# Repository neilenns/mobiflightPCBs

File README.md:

# mobiflightPCBs
Assorted PCBs for Mobiflight

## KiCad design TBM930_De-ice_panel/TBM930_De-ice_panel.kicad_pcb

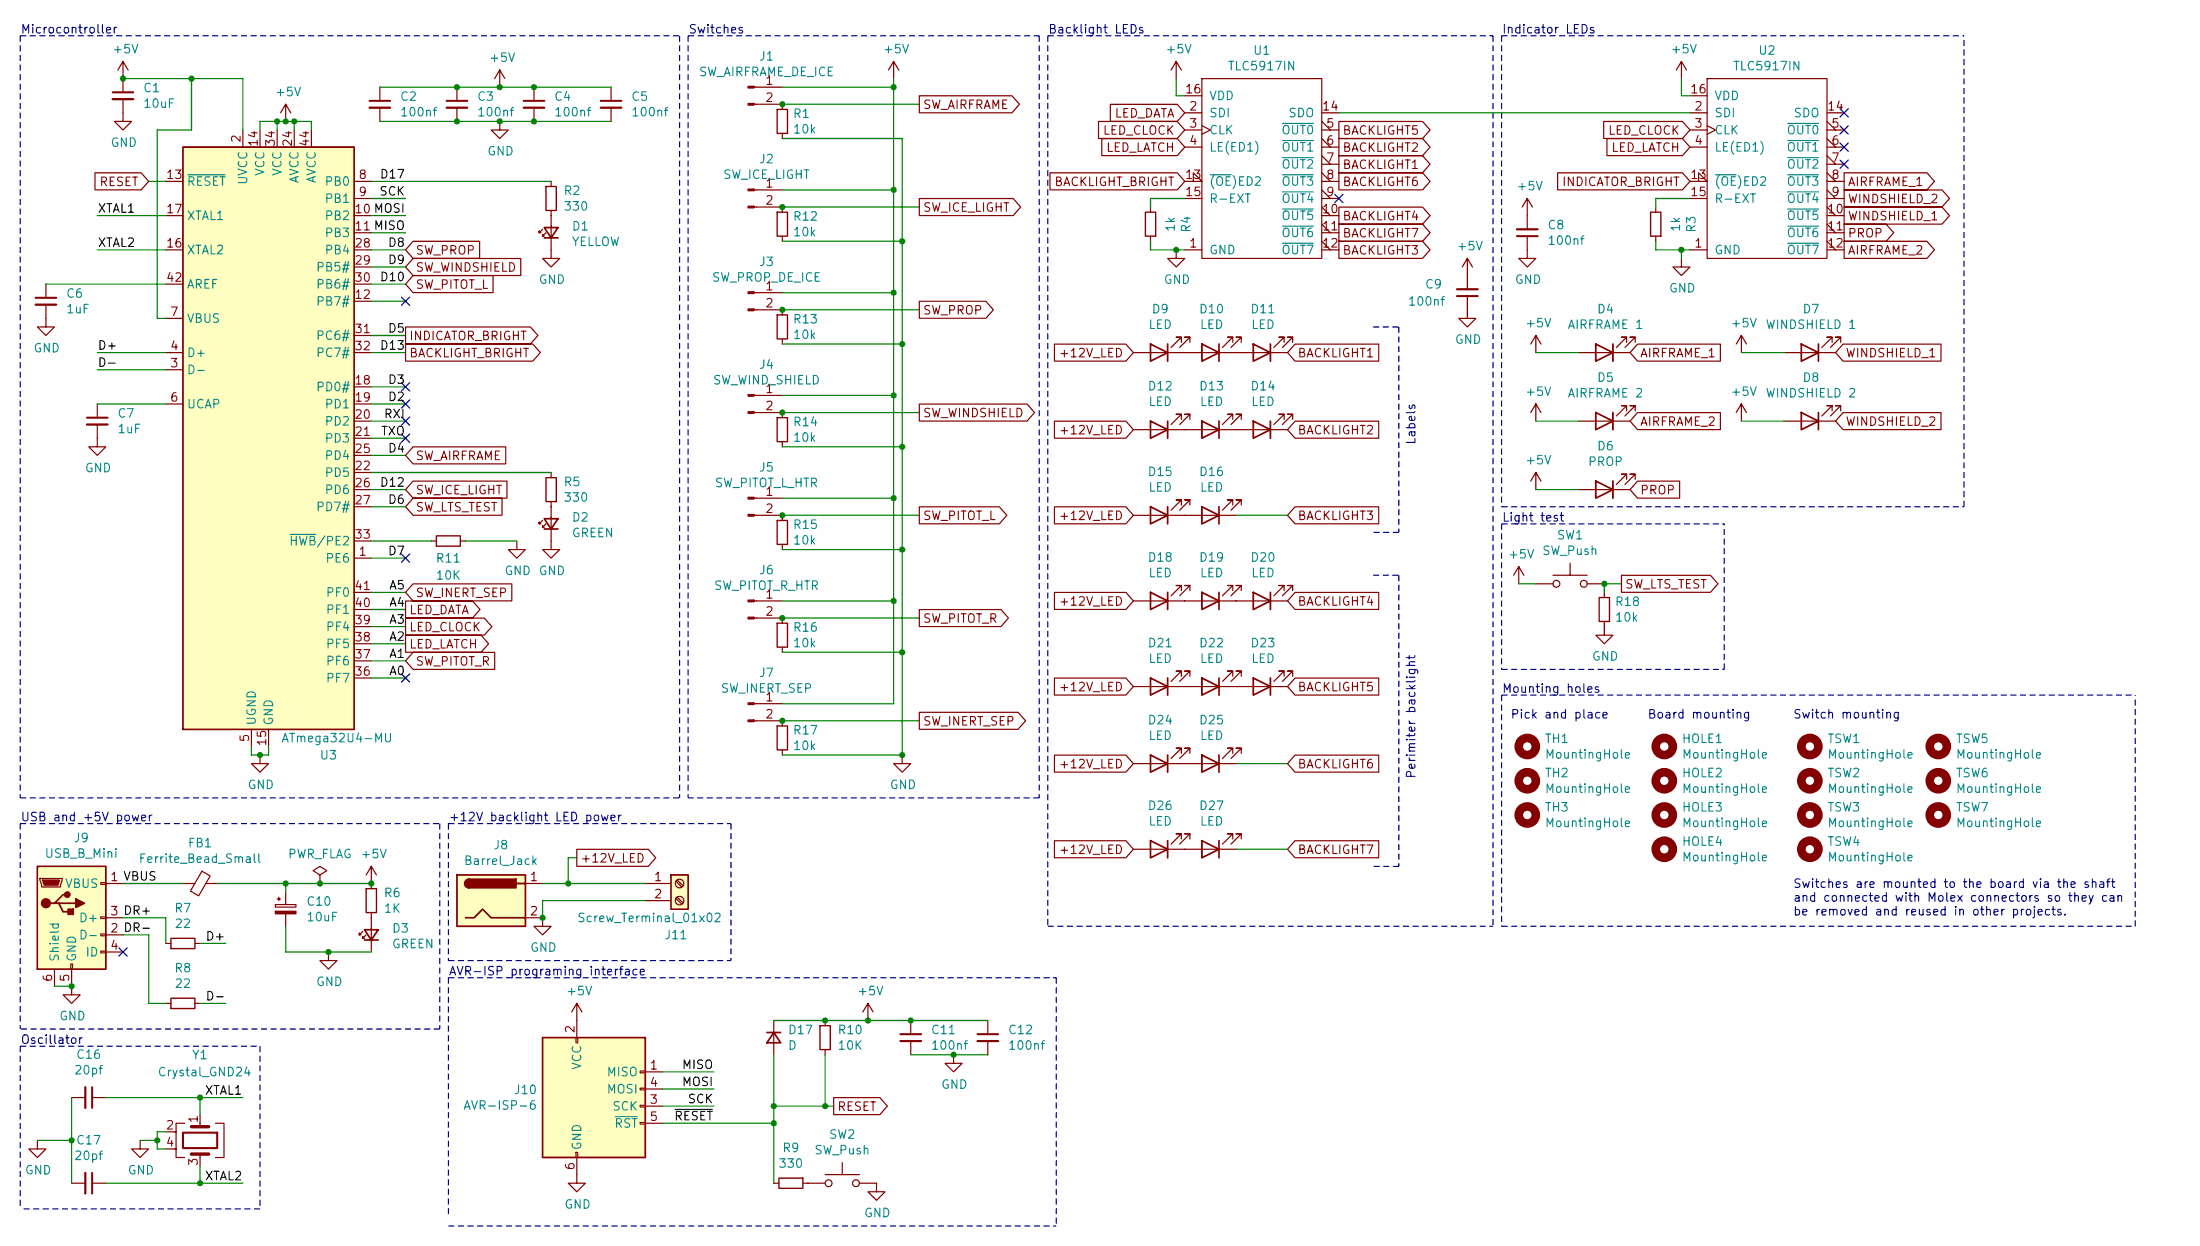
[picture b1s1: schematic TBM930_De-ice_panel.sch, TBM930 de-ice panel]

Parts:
C1, C10: 10uF; C_0603_1608Metric; JLC 0603
C2, C3, C4, C5, C8, C9, C11, C12: 100nf; C_0402_1005Metric; JLC 0402
C6, C7: 1uF; C_0402_1005Metric; JLC 0402
C16, C17: 20pf; C_0402_1005Metric; JLC 0402
D1: YELLOW; LED_0603_1608Metric; JLC LED_0603
D2, D3: GREEN; LED_0603_1608Metric; JLC LED_0603
D4: AIRFRAME 1; LED_D5.0mm
D5: AIRFRAME 2; LED_D5.0mm
D6: PROP; LED_D5.0mm
D7: WINDSHIELD 1; LED_D5.0mm
D8: WINDSHIELD 2; LED_D5.0mm
D9, D10, D11, D12, D13, D14, D15, D16, D18, D19, D20, D21, D22, D23, D24, D25, D26, D27: LED; LED_1206_3216Metric_Pad1.42x1.75mm_HandSolder
D17: D; D_SOD-323F; JLC SOD-323F
FB1: Ferrite_Bead_Small; C_0805_2012Metric; JLC 0805
HOLE1, HOLE2, HOLE3, HOLE4: MountingHole; MountingHole_3.2mm_M3
J1: SW_AIRFRAME_DE_ICE; Molex_KK-254_AE-6410-02A_1x02_P2.54mm_Vertical
J2: SW_ICE_LIGHT; Molex_KK-254_AE-6410-02A_1x02_P2.54mm_Vertical
J3: SW_PROP_DE_ICE; Molex_KK-254_AE-6410-02A_1x02_P2.54mm_Vertical
J4: SW_WIND_SHIELD; Molex_KK-254_AE-6410-02A_1x02_P2.54mm_Vertical
J5: SW_PITOT_L_HTR; Molex_KK-254_AE-6410-02A_1x02_P2.54mm_Vertical
J6: SW_PITOT_R_HTR; Molex_KK-254_AE-6410-02A_1x02_P2.54mm_Vertical
J7: SW_INERT_SEP; Molex_KK-254_AE-6410-02A_1x02_P2.54mm_Vertical
J8: Barrel_Jack; BarrelJack_Horizontal
J9: USB_B_Mini; USB_B_Mini_Amphenol_UE25BE5510H
J10: AVR-ISP-6; PinHeader_2x03_P2.54mm_Vertical
J11: Screw_Terminal_01x02; TerminalBlock_Phoenix_PT-1,5-2-5.0-H_1x02_P5.00mm_Horizontal
R1, R12, R13, R14, R15, R16, R17, R18: 10k; R_0402_1005Metric; JLC 0402
R2, R5, R9: 330; R_0402_1005Metric; JLC 0402
R3, R4: 1k; R_Axial_DIN0207_L6.3mm_D2.5mm_P7.62mm_Horizontal
R6: 1K; R_0402_1005Metric; JLC 0402
R7, R8: 22; R_0402_1005Metric; JLC 0402
R10, R11: 10K; R_0402_1005Metric; JLC 0402
SW1: SW_Push; SW_PUSH_6mm_H9.5mm
SW2: SW_Push; SW_PUSH_6mm_H4.3mm
TH1, TH2, TH3: MountingHole; JLCPCB_Tooling_Hole
TSW1, TSW2, TSW3, TSW4, TSW5, TSW6, TSW7: MountingHole; MiniToggleSPDT_screw_mount
U1, U2: TLC5917IN; DIP-16_W7.62mm
U3: ATmega32U4-MU; TQFP-44-1EP_10x10mm_P0.8mm_EP4.5x4.5mm
Y1: Crystal_GND24; Crystal_SMD_3225-4Pin_3.2x2.5mm; JLC SMD-CRY-3225_4P

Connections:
+5V: C1.1, C2.1, C3.1, C4.1, C5.1, C8.2, C9.2, C10.1, C11.1, C12.1, D4.2 (A), D5.2 (A), D6.2 (A), D7.2 (A), D8.2 (A), D17.1 (K), FB1.1, J1.1, J2.1, J3.1, J4.1, J5.1, J6.1, J7.1, J10.2 (VCC), R6.1, R10.1, SW1.1, U1.16 (VDD), U2.16 (VDD), U3.2 (UVCC), U3.7 (VBUS), U3.14 (VCC), U3.24 (AVCC), U3.34 (VCC), U3.44 (AVCC)
+12V_LED: D9.2 (A), D12.2 (A), D15.2 (A), D18.2 (A), D21.2 (A), D24.2 (A), D26.2 (A), J8.1, J11.1
/A0: U3.36 (PF7)
/D2: U3.19 (PD1)
/D3: U3.18 (PD0#)
/D7: U3.1 (PE6)
/D17: R2.1, U3.8 (PB0)
/D+: R7.2, U3.4 (D+)
/D-: R8.2, U3.3 (D-)
/DR+: J9.3 (D+), R7.1
/DR-: J9.2 (D-), R8.1
/MISO: J10.1 (MISO), U3.11 (PB3)
/MOSI: J10.4 (MOSI), U3.10 (PB2)
/RXI: U3.20 (PD2)
/SCK: J10.3 (SCK), U3.9 (PB1)
/TXO: U3.21 (PD3)
/VBUS: FB1.2, J9.1 (VBUS)
/XTAL1: C16.1, U3.17 (XTAL1), Y1.1
/XTAL2: C17.1, U3.16 (XTAL2), Y1.3
AIRFRAME_1: D4.1 (K), U2.8 (~OUT3)
AIRFRAME_2: D5.1 (K), U2.12 (~OUT7)
BACKLIGHT1: D11.1 (K), U1.7 (~OUT2)
BACKLIGHT2: D14.1 (K), U1.6 (~OUT1)
BACKLIGHT3: D16.1 (K), U1.12 (~OUT7)
BACKLIGHT4: D20.1 (K), U1.10 (~OUT5)
BACKLIGHT5: D23.1 (K), U1.5 (~OUT0)
BACKLIGHT6: D25.1 (K), U1.8 (~OUT3)
BACKLIGHT7: D27.1 (K), U1.11 (~OUT6)
BACKLIGHT_BRIGHT: U1.13 (~(OE)ED2), U3.32 (PC7#)
GND: C1.2, C2.2, C3.2, C4.2, C5.2, C6.2, C7.2, C8.1, C9.1, C10.2, C11.2, C12.2, C16.2, C17.2, D1.1 (K), D2.1 (K), D3.1 (K), J8.2, J9.5 (GND), J9.6 (Shield), J10.6 (GND), J11.2, R1.2, R3.1, R4.1, R11.2, R12.2, R13.2, R14.2, R15.2, R16.2, R17.2, R18.1, SW2.2, U1.1 (GND), U2.1 (GND), U3.5 (UGND), U3.15 (GND), U3.23 (GND), U3.35 (GND), U3.43 (GND), U3.45 (GND), Y1.2, Y1.4
INDICATOR_BRIGHT: U2.13 (~(OE)ED2), U3.31 (PC6#)
LED_CLOCK: U1.3 (CLK), U2.3 (CLK), U3.39 (PF4)
LED_DATA: U1.2 (SDI), U3.40 (PF1)
LED_LATCH: U1.4 (LE(ED1)), U2.4 (LE(ED1)), U3.38 (PF5)
unnamed: C6.1, U3.42 (AREF)
unnamed: C7.1, U3.6 (UCAP)
unnamed: D1.2 (A), R2.2
unnamed: D2.2 (A), R5.1
unnamed: D3.2 (A), R6.2
unnamed: D10.1 (K), D11.2 (A)
unnamed: D9.1 (K), D10.2 (A)
unnamed: D12.1 (K), D13.2 (A)
unnamed: D13.1 (K), D14.2 (A)
unnamed: D15.1 (K), D16.2 (A)
unnamed: D18.1 (K), D19.2 (A)
unnamed: D19.1 (K), D20.2 (A)
unnamed: D21.1 (K), D22.2 (A)
unnamed: D22.1 (K), D23.2 (A)
unnamed: D24.1 (K), D25.2 (A)
unnamed: D26.1 (K), D27.2 (A)
unnamed: R3.2, U2.15 (R-EXT)
unnamed: R4.2, U1.15 (R-EXT)
unnamed: R5.2, U3.22 (PD5)
unnamed: R9.1, SW2.1
unnamed: R11.1, U3.33 (~HWB~/PE2)
unnamed: U1.14 (SDO), U2.2 (SDI)
PROP: D6.1 (K), U2.11 (~OUT6)
RESET: D17.2 (A), J10.5 (~RST), R9.2, R10.2, U3.13 (~RESET)
SW_AIRFRAME: J1.2, R1.1, U3.25 (PD4)
SW_ICE_LIGHT: J2.2, R12.1, U3.26 (PD6)
SW_INERT_SEP: J7.2, R17.1, U3.41 (PF0)
SW_LTS_TEST: R18.2, SW1.2, U3.27 (PD7#)
SW_PITOT_L: J5.2, R15.1, U3.30 (PB6#)
SW_PITOT_R: J6.2, R16.1, U3.37 (PF6)
SW_PROP: J3.2, R13.1, U3.28 (PB4)
SW_WINDSHIELD: J4.2, R14.1, U3.29 (PB5#)
WINDSHIELD_1: D7.1 (K), U2.10 (~OUT5)
WINDSHIELD_2: D8.1 (K), U2.9 (~OUT4)

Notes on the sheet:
Switches
Switches are mounted to the board via the shaft and connected with Molex connectors so they can be removed and reused in other projects.
+12V backlight LED power
Backlight LEDs
USB and +5V power
Oscillator
Microcontroller
AVR-ISP programing interface
Labels
Perimiter backlight
Light test
Indicator LEDs
Pick and place
Board mounting
Switch mounting
Mounting holes

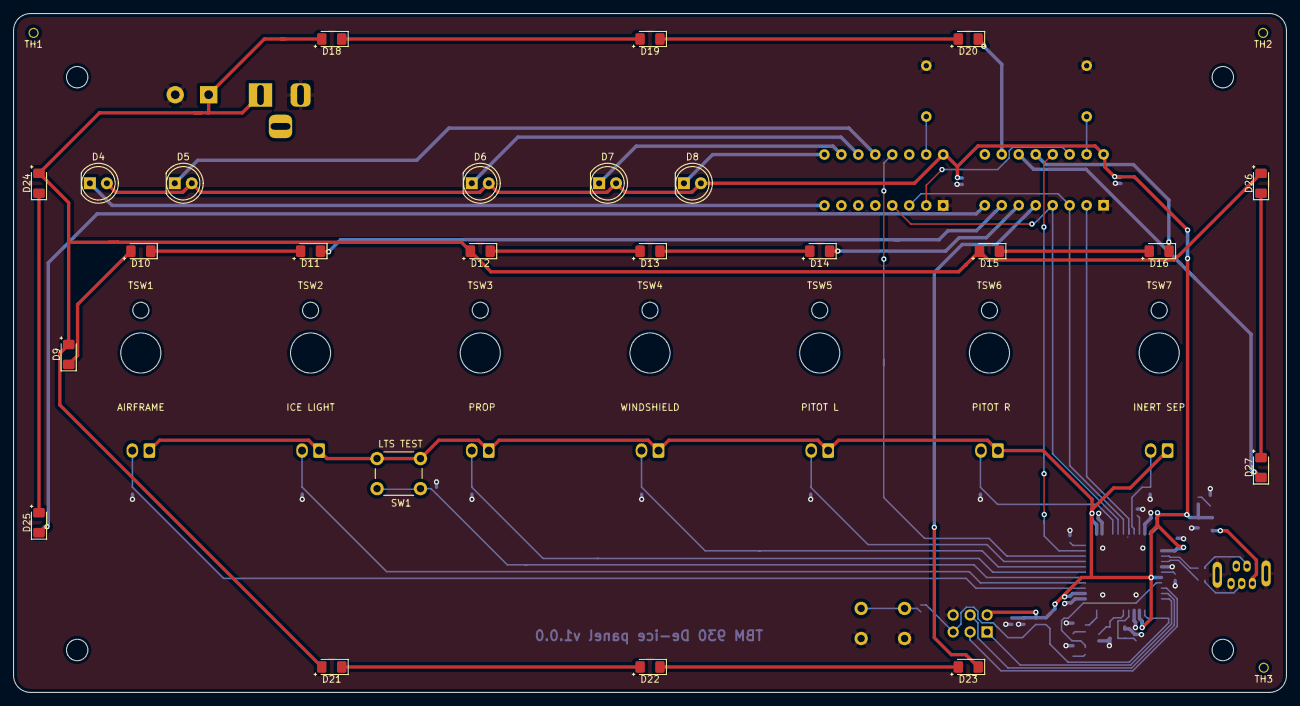
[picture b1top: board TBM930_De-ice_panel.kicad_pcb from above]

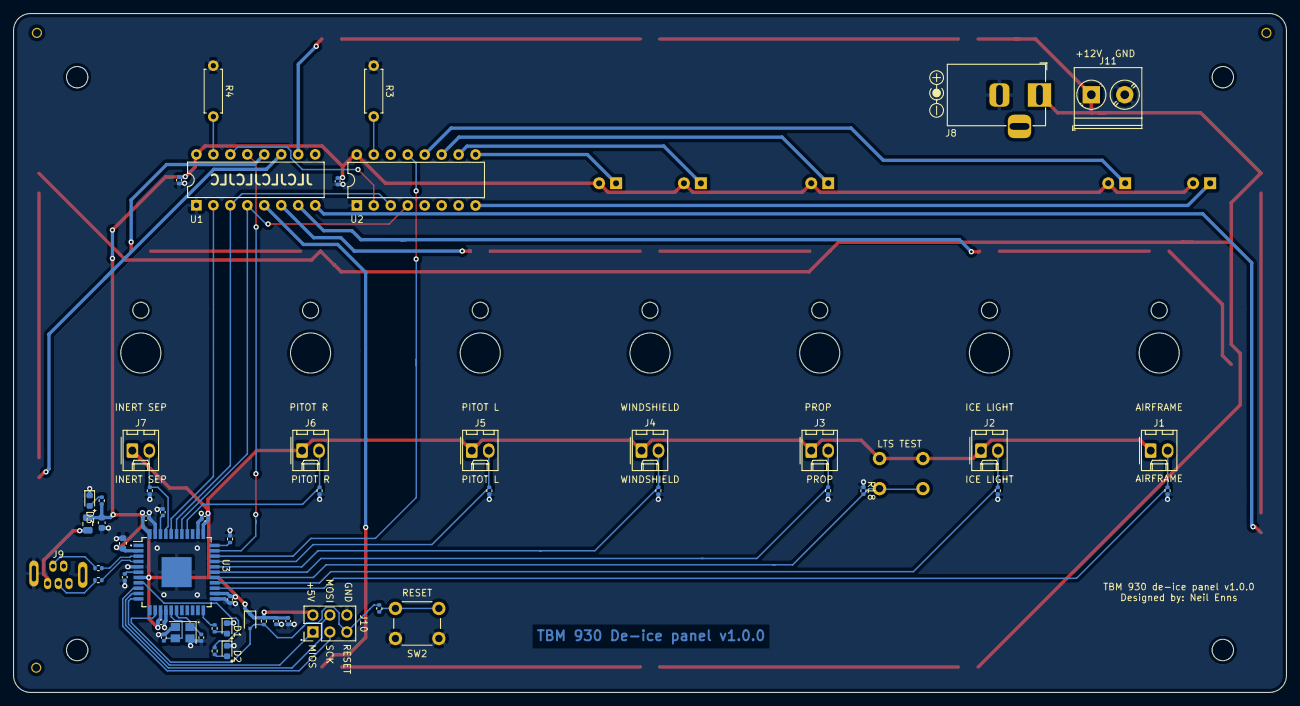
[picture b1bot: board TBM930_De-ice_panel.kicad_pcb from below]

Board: 2 copper layers, 190.5 x 101.6 mm, 91 parts (53 on the bottom side), 62 nets.

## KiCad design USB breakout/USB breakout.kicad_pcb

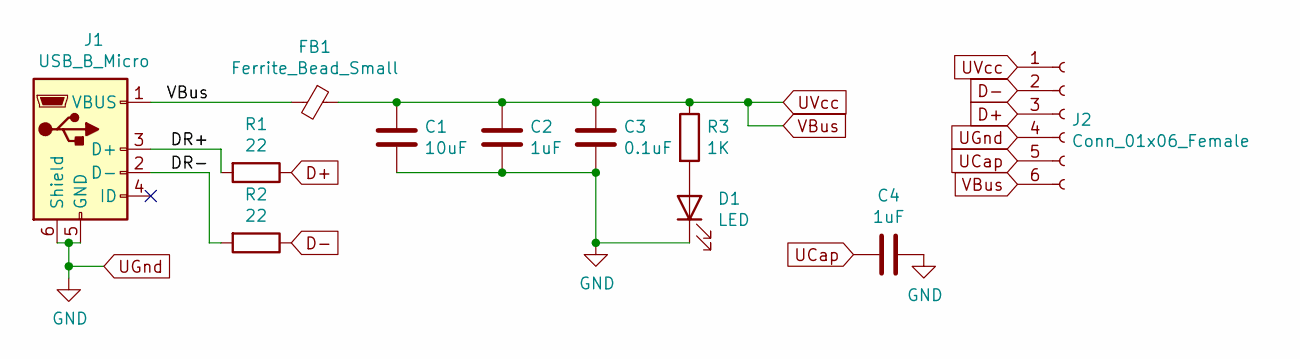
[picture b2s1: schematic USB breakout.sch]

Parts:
C1: 10uF; C_1206_3216Metric_Pad1.33x1.80mm_HandSolder
C2, C4: 1uF; C_1206_3216Metric_Pad1.33x1.80mm_HandSolder
C3: 0.1uF; C_1206_3216Metric_Pad1.33x1.80mm_HandSolder
D1: LED; LED_1206_3216Metric_Pad1.42x1.75mm_HandSolder
FB1: Ferrite_Bead_Small; R_1206_3216Metric_Pad1.30x1.75mm_HandSolder
J1: USB_B_Micro; USB_Micro-B_Amphenol_10118194_Horizontal
J2: Conn_01x06_Female; PinHeader_1x06_P2.54mm_Vertical
R1, R2: 22; R_1206_3216Metric_Pad1.30x1.75mm_HandSolder
R3: 1K; R_1206_3216Metric_Pad1.30x1.75mm_HandSolder

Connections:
/DR+: J1.3 (D+), R1.2
/DR-: J1.2 (D-), R2.2
D+: J2.3, R1.1
D-: J2.2, R2.1
unnamed: D1.2 (A), R3.2
UCap: C4.2, J2.5
UGnd: C1.1, C2.2, C3.2, C4.1, D1.1 (K), J1.5 (GND), J1.6 (Shield), J2.4
UVcc: C1.2, C2.1, C3.1, FB1.1, FB1.2, J1.1 (VBUS), J2.1, J2.6, R3.1

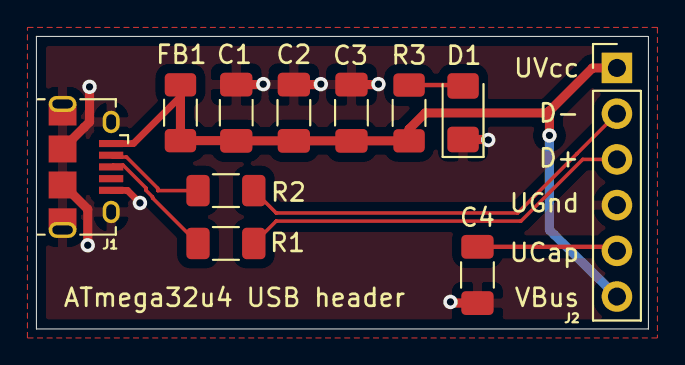
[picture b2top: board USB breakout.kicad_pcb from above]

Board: 2 copper layers, 34.0 x 16.2 mm, 11 parts (0 on the bottom side), 8 nets.

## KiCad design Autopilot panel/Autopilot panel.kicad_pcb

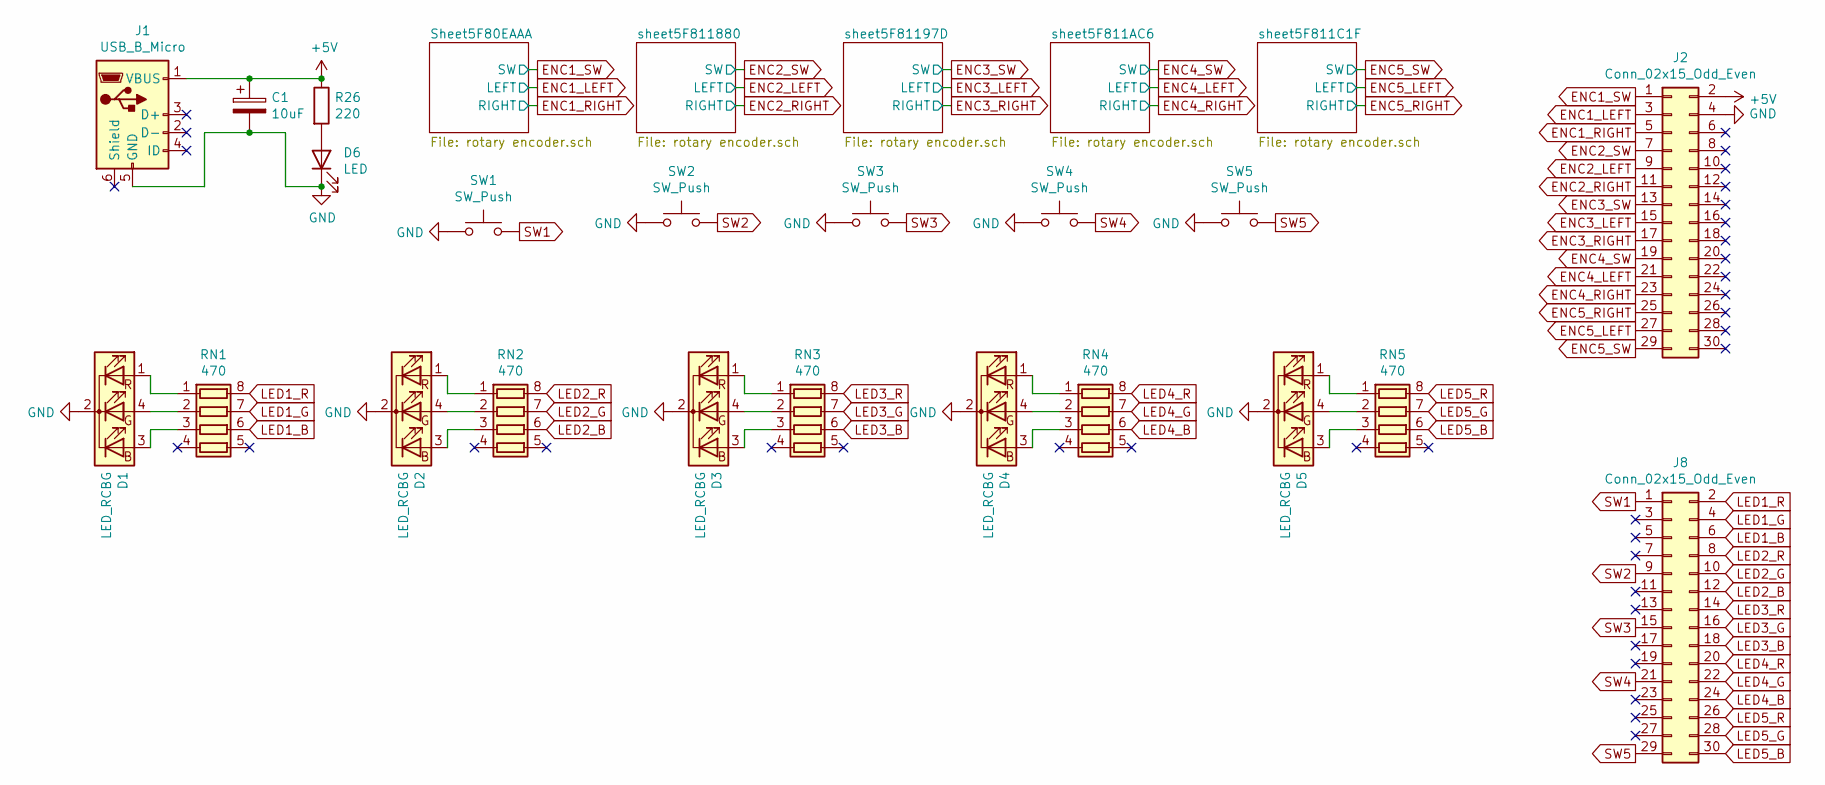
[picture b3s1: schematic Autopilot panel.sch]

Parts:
C1: 10uF; CP_Radial_D5.0mm_P2.00mm; LCSC C7171
D1, D2, D3, D4, D5: LED_RCBG; LED_D5.0mm-4_RGB
D6: LED; LED_0805_2012Metric_Pad1.15x1.40mm_HandSolder; LCSC C2293
J1: USB_B_Micro; USB_Micro-B_Molex-105017-0001
J2, J8: Conn_02x15_Odd_Even; PinHeader_2x15_P2.54mm_Vertical
R26: 220; R_0805_2012Metric_Pad1.15x1.40mm_HandSolder; LCSC C17557
RN1, RN2, RN3, RN4, RN5: 470; R_Array_Convex_4x0603; LCSC C25510
SW1, SW2, SW3, SW4, SW5: SW_Push; SW_PUSH_6mm_H8mm

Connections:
+5V: C1.1, J1.1 (VBUS), J2.2, R26.1; also elsewhere on the board
ENC1_LEFT: J2.3; also elsewhere on the board
ENC1_RIGHT: J2.5; also elsewhere on the board
ENC1_SW: J2.1; also elsewhere on the board
ENC2_LEFT: J2.9; also elsewhere on the board
ENC2_RIGHT: J2.11; also elsewhere on the board
ENC2_SW: J2.7; also elsewhere on the board
ENC3_LEFT: J2.15; also elsewhere on the board
ENC3_RIGHT: J2.17; also elsewhere on the board
ENC3_SW: J2.13; also elsewhere on the board
ENC4_LEFT: J2.21; also elsewhere on the board
ENC4_RIGHT: J2.23; also elsewhere on the board
ENC4_SW: J2.19; also elsewhere on the board
ENC5_LEFT: J2.27; also elsewhere on the board
ENC5_RIGHT: J2.25; also elsewhere on the board
ENC5_SW: J2.29; also elsewhere on the board
GND: C1.2, D1.2 (K), D2.2 (K), D3.2 (K), D4.2 (K), D5.2 (K), D6.1 (K), J1.5 (GND), J2.4, SW1.1, SW2.1, SW3.1, SW4.1, SW5.1; also elsewhere on the board
LED1_B: J8.6, RN1.6 (R3.2)
LED1_G: J8.4, RN1.7 (R2.2)
LED1_R: J8.2, RN1.8 (R1.2)
LED2_B: J8.12, RN2.6 (R3.2)
LED2_G: J8.10, RN2.7 (R2.2)
LED2_R: J8.8, RN2.8 (R1.2)
LED3_B: J8.18, RN3.6 (R3.2)
LED3_G: J8.16, RN3.7 (R2.2)
LED3_R: J8.14, RN3.8 (R1.2)
LED4_B: J8.24, RN4.6 (R3.2)
LED4_G: J8.22, RN4.7 (R2.2)
LED4_R: J8.20, RN4.8 (R1.2)
LED5_B: J8.30, RN5.6 (R3.2)
LED5_G: J8.28, RN5.7 (R2.2)
LED5_R: J8.26, RN5.8 (R1.2)
unnamed: D1.1 (RA), RN1.1 (R1.1)
unnamed: D1.3 (BA), RN1.3 (R3.1)
unnamed: D1.4 (GA), RN1.2 (R2.1)
unnamed: D2.1 (RA), RN2.1 (R1.1)
unnamed: D2.3 (BA), RN2.3 (R3.1)
unnamed: D2.4 (GA), RN2.2 (R2.1)
unnamed: D3.1 (RA), RN3.1 (R1.1)
unnamed: D3.3 (BA), RN3.3 (R3.1)
unnamed: D3.4 (GA), RN3.2 (R2.1)
unnamed: D4.1 (RA), RN4.1 (R1.1)
unnamed: D4.3 (BA), RN4.3 (R3.1)
unnamed: D4.4 (GA), RN4.2 (R2.1)
unnamed: D5.1 (RA), RN5.1 (R1.1)
unnamed: D5.3 (BA), RN5.3 (R3.1)
unnamed: D5.4 (GA), RN5.2 (R2.1)
unnamed: D6.2 (A), R26.2
SW1: J8.1, SW1.2
SW2: J8.9, SW2.2
SW3: J8.15, SW3.2
SW4: J8.21, SW4.2
SW5: J8.29, SW5.2

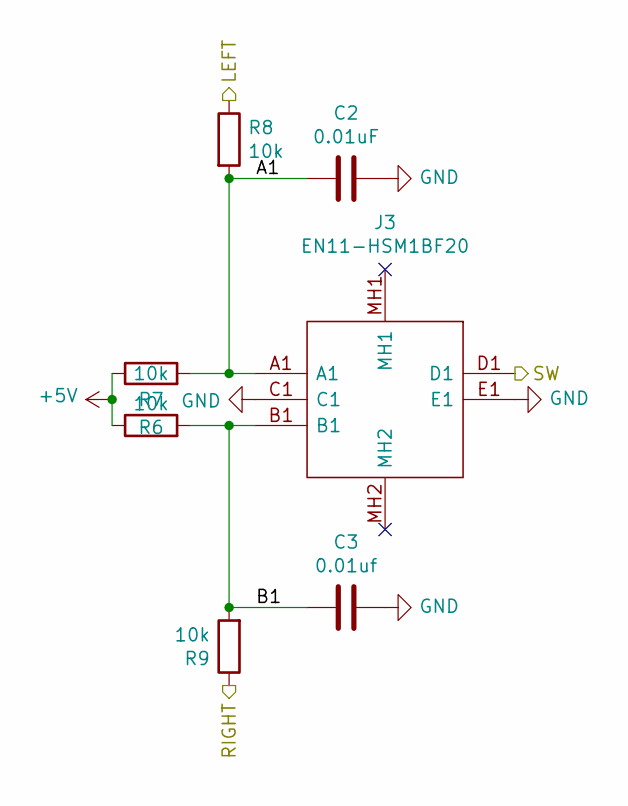
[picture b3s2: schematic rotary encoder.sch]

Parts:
C2: 0.01uF; C_0805_2012Metric_Pad1.15x1.40mm_HandSolder; LCSC C1710
C3: 0.01uf; C_0805_2012Metric_Pad1.15x1.40mm_HandSolder; LCSC C1710
J3: EN11-HSM1BF20; EN11HSM1BF20; Mouser Part Number 858-EN11-HSM1BF20
R6, R7, R8, R9: 10k; R_0805_2012Metric_Pad1.15x1.40mm_HandSolder; LCSC C17414

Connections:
+5V: R6.1, R7.1; also elsewhere on the board
/Sheet5F80EAAA/A1: C2.2, J3.A1, R6.2, R8.2
/Sheet5F80EAAA/B1: C3.2, J3.B1, R7.2, R9.2
ENC1_LEFT: R8.1; also elsewhere on the board
ENC1_RIGHT: R9.1; also elsewhere on the board
ENC1_SW: J3.D1; also elsewhere on the board
GND: C2.1, C3.1, J3.C1, J3.E1; also elsewhere on the board

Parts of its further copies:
C4, C6, C8, C10: 0.01uF; C_0805_2012Metric_Pad1.15x1.40mm_HandSolder; LCSC C1710
C5, C7, C9, C11: 0.01uf; C_0805_2012Metric_Pad1.15x1.40mm_HandSolder; LCSC C1710
J4, J5, J6, J7: EN11-HSM1BF20; EN11HSM1BF20; Mouser Part Number 858-EN11-HSM1BF20
R10, R11, R12, R13, R14, R15, R16, R17, R18, R19, R20, R21, R22, R23, R24, R25: 10k; R_0805_2012Metric_Pad1.15x1.40mm_HandSolder; LCSC C17414

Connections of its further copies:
+5V: R10.1, R11.1, R14.1, R15.1, R18.1, R19.1, R22.1, R23.1; also elsewhere on the board
/sheet5F811AC6/A1: C8.2, J6.A1, R18.2, R20.2
/sheet5F811AC6/B1: C9.2, J6.B1, R19.2, R21.2
/sheet5F811C1F/A1: C10.2, J7.A1, R22.2, R24.2
/sheet5F811C1F/B1: C11.2, J7.B1, R23.2, R25.2
/sheet5F81197D/A1: C6.2, J5.A1, R14.2, R16.2
/sheet5F81197D/B1: C7.2, J5.B1, R15.2, R17.2
/sheet5F811880/A1: C4.2, J4.A1, R10.2, R12.2
/sheet5F811880/B1: C5.2, J4.B1, R11.2, R13.2
ENC2_LEFT: R12.1; also elsewhere on the board
ENC2_RIGHT: R13.1; also elsewhere on the board
ENC2_SW: J4.D1; also elsewhere on the board
ENC3_LEFT: R16.1; also elsewhere on the board
ENC3_RIGHT: R17.1; also elsewhere on the board
ENC3_SW: J5.D1; also elsewhere on the board
ENC4_LEFT: R20.1; also elsewhere on the board
ENC4_RIGHT: R21.1; also elsewhere on the board
ENC4_SW: J6.D1; also elsewhere on the board
ENC5_LEFT: R24.1; also elsewhere on the board
ENC5_RIGHT: R25.1; also elsewhere on the board
ENC5_SW: J7.D1; also elsewhere on the board
GND: C4.1, C5.1, C6.1, C7.1, C8.1, C9.1, C10.1, C11.1, J4.C1, J4.E1, J5.C1, J5.E1, J6.C1, J6.E1, J7.C1, J7.E1; also elsewhere on the board

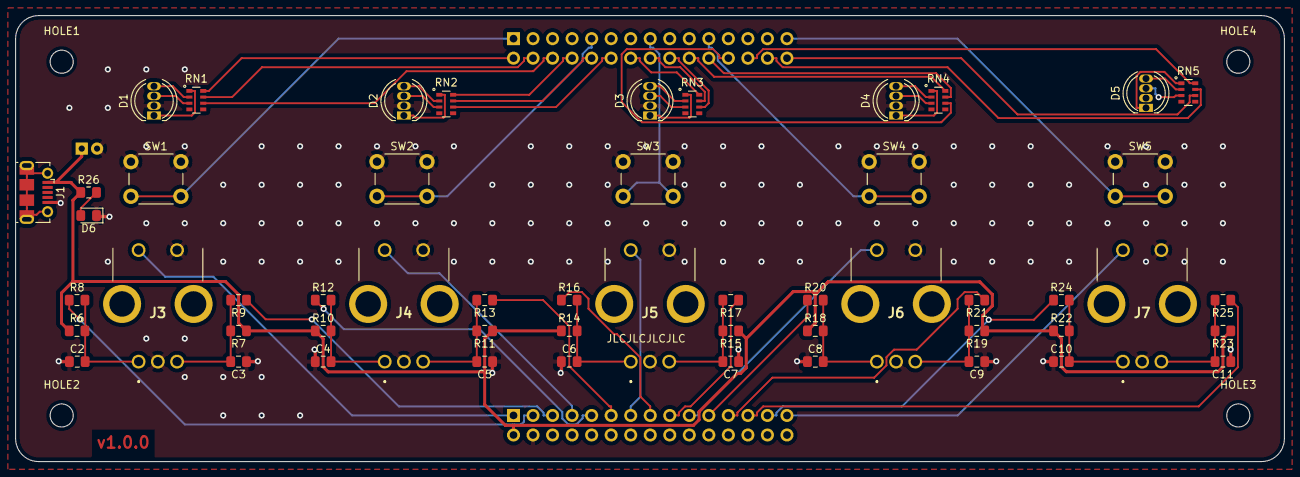
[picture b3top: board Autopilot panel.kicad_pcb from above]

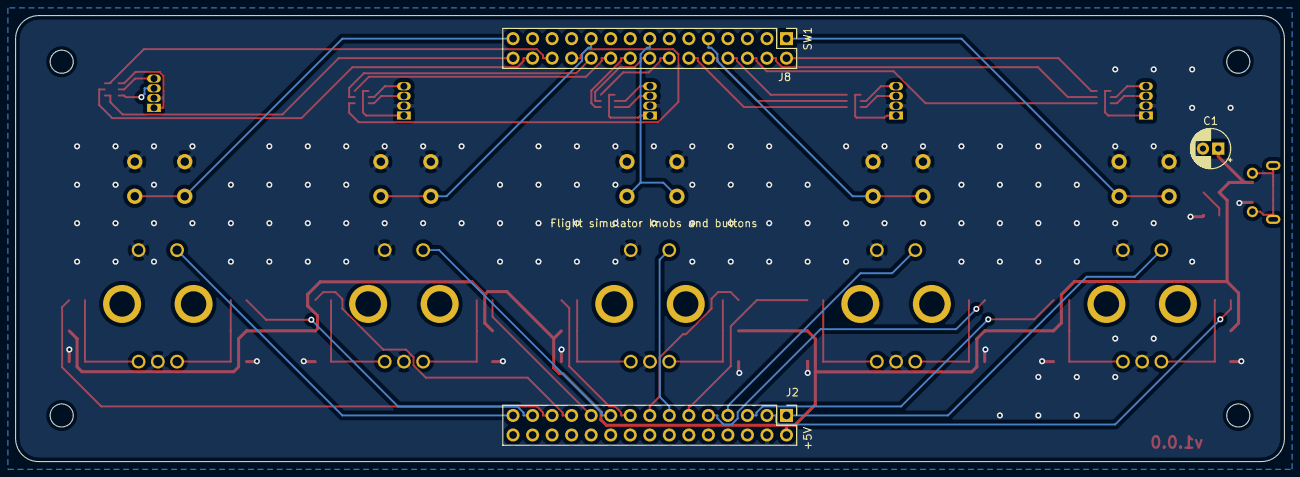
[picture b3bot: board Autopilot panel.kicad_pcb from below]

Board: 2 copper layers, 165.0 x 58.0 mm, 60 parts (3 on the bottom side), 63 nets.

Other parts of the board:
HOLE1, HOLE2, HOLE3, HOLE4: MountingHole_3mm

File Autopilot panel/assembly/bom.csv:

Comment,Designator,Footprint,LCSC
"10uF","C1","Capacitor_Tantalum_SMD:CP_EIA-3216-18_Kemet-A","C7171"
"0.01uF","C2,C4,C6,C8,C10","Capacitor_SMD:C_0805_2012Metric_Pad1.15x1.40mm_HandSolder"," C1710"
"0.01uf","C3,C5,C7,C9,C11","Capacitor_SMD:C_0805_2012Metric_Pad1.15x1.40mm_HandSolder"," C1710"
"LED_RCBG","D1,D2,D3,D4,D5","LED_THT:LED_D5.0mm-4_RGB",""
"LED","D6","LED_SMD:LED_0805_2012Metric_Pad1.15x1.40mm_HandSolder","C2293"
"USB_B_Micro","J1","Connector_USB:USB_Micro-B_Molex-105017-0001",""
"Conn_02x15_Odd_Even","J2,J8","Connector_PinHeader_2.54mm:PinHeader_2x15_P2.54mm_Vertical",""
"EN11-HSM1BF20","J3,J4,J5,J6,J7","SamacSys_Parts:EN11HSM1BF20",""
"220","R26","Resistor_SMD:R_0805_2012Metric_Pad1.15x1.40mm_HandSolder"," C17557"
"10k","R6,R7,R8,R9,R10,R11,R12,R13,R14,R15,R16,R17,R18,R19,R20,R21,R22,R23,R24,R25","Resistor_SMD:R_0805_2012Metric_Pad1.15x1.40mm_HandSolder","C17414"
"470","RN1,RN2,RN3,RN4,RN5","Resistor_SMD:R_Array_Convex_4x0603","C25510"
"SW_Push","SW1,SW2,SW3,SW4,SW5","Button_Switch_THT:SW_PUSH_6mm_H8mm",""

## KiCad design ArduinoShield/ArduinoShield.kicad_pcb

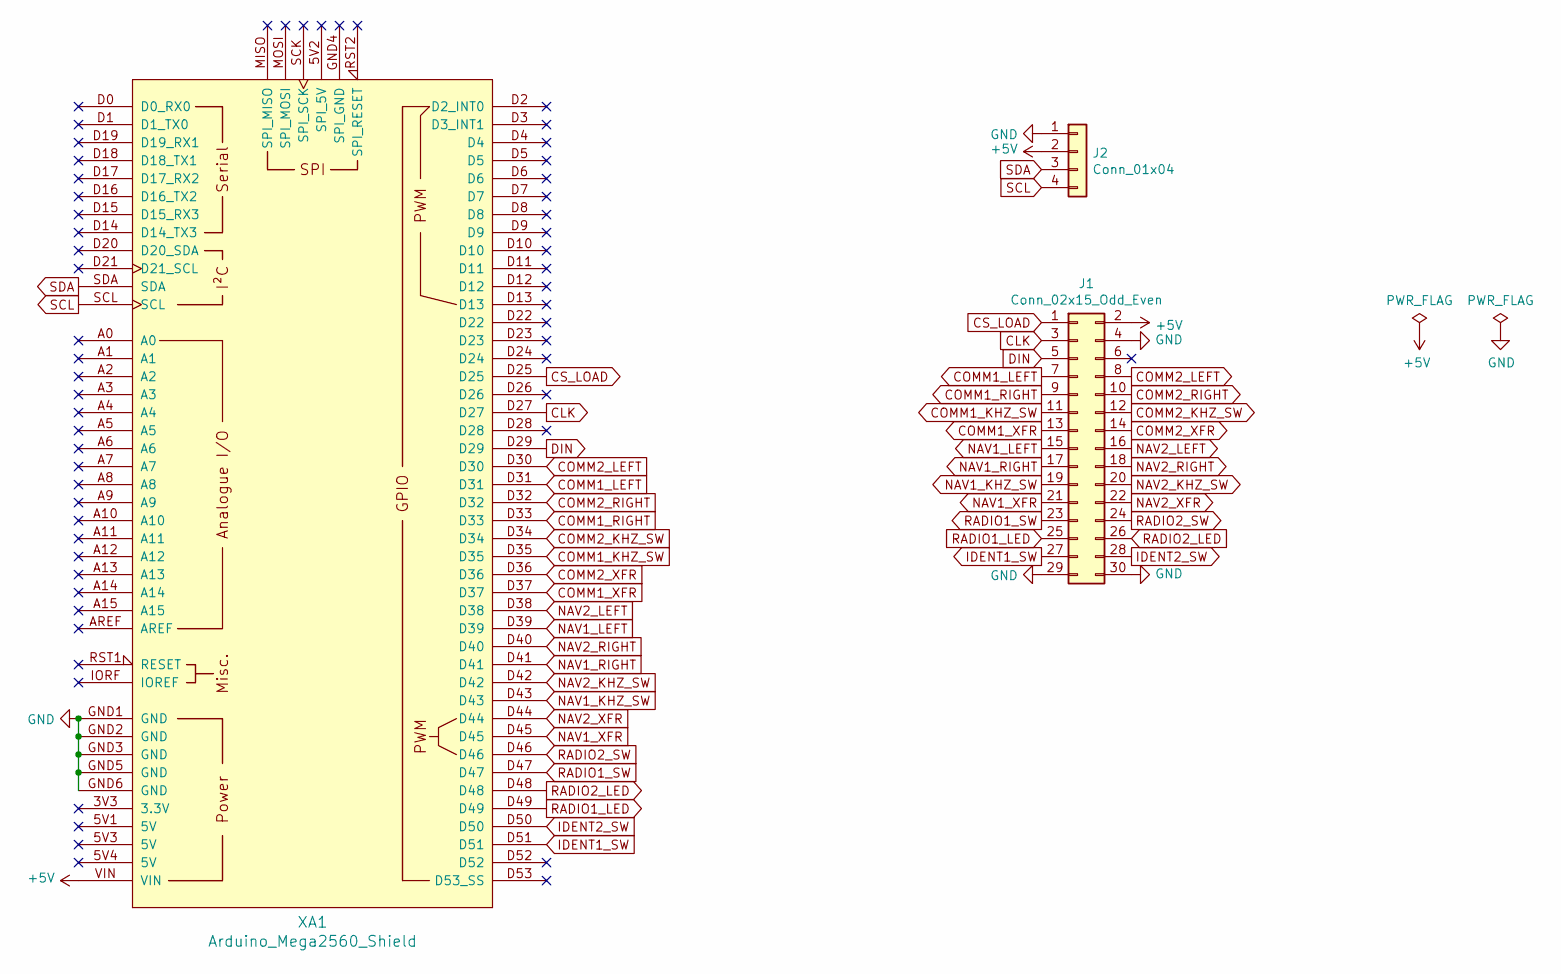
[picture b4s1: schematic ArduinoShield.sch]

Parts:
J1: Conn_02x15_Odd_Even; PinSocket_2x15_P2.54mm_Vertical
J2: Conn_01x04; Molex_KK-254_AE-6410-04A_1x04_P2.54mm_Horizontal
XA1: Arduino_Mega2560_Shield

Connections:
+5V: J1.2, J2.2, XA1.VIN
CLK: J1.3, XA1.D27
COMM1_KHZ_SW: J1.11, XA1.D35
COMM1_LEFT: J1.7, XA1.D31
COMM1_RIGHT: J1.9, XA1.D33
COMM1_XFR: J1.13, XA1.D37
COMM2_KHZ_SW: J1.12, XA1.D34
COMM2_LEFT: J1.8, XA1.D30
COMM2_RIGHT: J1.10, XA1.D32
COMM2_XFR: J1.14, XA1.D36
CS_LOAD: J1.1, XA1.D25
DIN: J1.5, XA1.D29
GND: J1.4, J1.29, J1.30, J2.1, XA1.GND1 (GND), XA1.GND2 (GND), XA1.GND3 (GND), XA1.GND5 (GND), XA1.GND6 (GND)
IDENT1_SW: J1.27, XA1.D51
IDENT2_SW: J1.28, XA1.D50
NAV1_KHZ_SW: J1.19, XA1.D43
NAV1_LEFT: J1.15, XA1.D39
NAV1_RIGHT: J1.17, XA1.D41
NAV1_XFR: J1.21, XA1.D45
NAV2_KHZ_SW: J1.20, XA1.D42
NAV2_LEFT: J1.16, XA1.D38
NAV2_RIGHT: J1.18, XA1.D40
NAV2_XFR: J1.22, XA1.D44
RADIO1_LED: J1.25, XA1.D49
RADIO1_SW: J1.23, XA1.D47
RADIO2_LED: J1.26, XA1.D48
RADIO2_SW: J1.24, XA1.D46
SCL: J2.4, XA1.SCL
SDA: J2.3, XA1.SDA

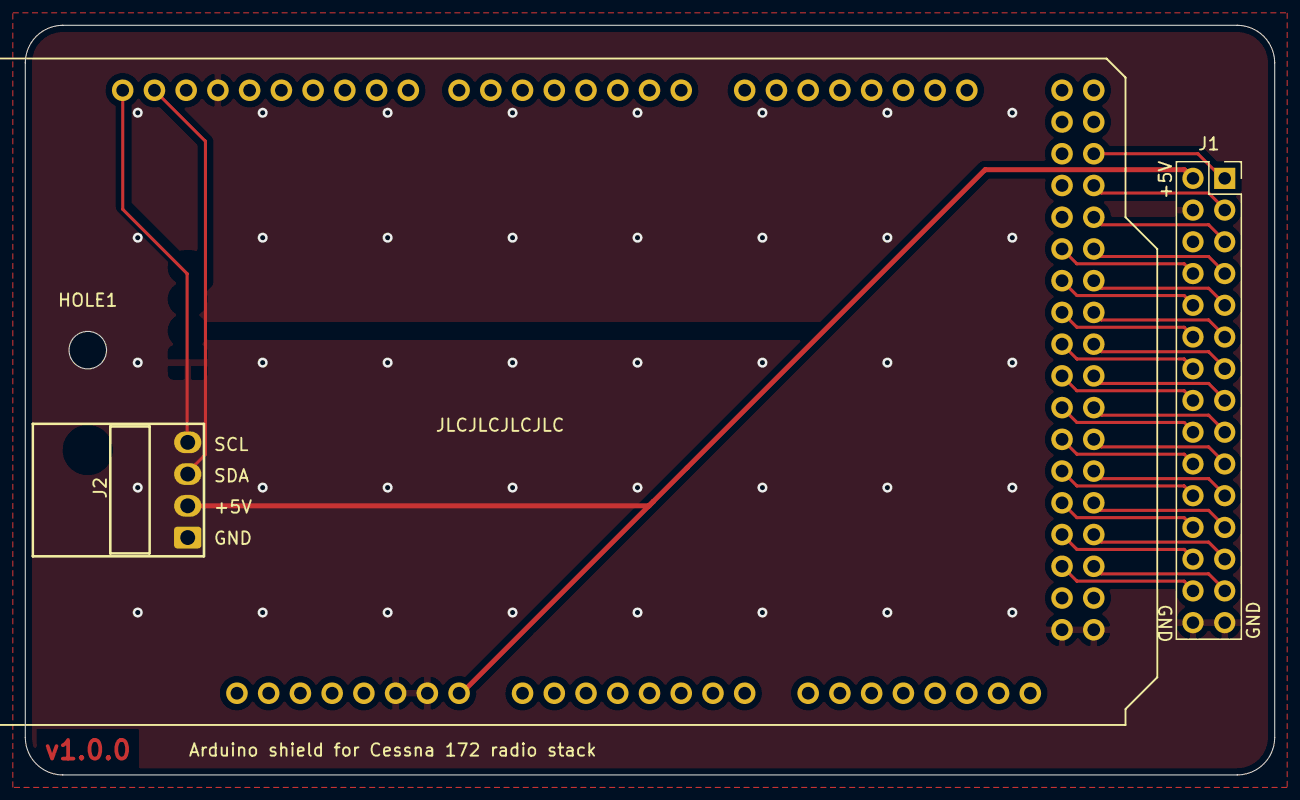
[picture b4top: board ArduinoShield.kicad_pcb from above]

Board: 2 copper layers, 100.0 x 60.0 mm, 4 parts (0 on the bottom side), 29 nets.

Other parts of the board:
HOLE1: MountingHole_3mm

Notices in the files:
TBM930_De-ice_panel/TBM930_De-ice_panel.sch:
Licensed under the MIT License
Copyright © 2021 Neil Enns
